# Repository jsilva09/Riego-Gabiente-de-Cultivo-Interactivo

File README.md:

# Riego-Gabiente-de-Cultivo-Interactivo

## Integrantes

- James Mauricio Daza Obando
- Julián Andrés Silva Cuadros
- Ivan Leonardo Tamayo Pérez

## Introducción

El grupo de riego es el encargado de suministrar agua a la planta según sus requerimientos específicos, así como también se encarga de proporcionar los nutrientes básicos necesarios para el correcto desarrollo y crecimiento de la misma.

Se llevará a cabo el método de fertirriego, el cual consiste en suministrar los fertilizantes requeridos por la planta en conjunto con el agua de riego [1]. Este método presenta varias ventajas, entre las cuales se encuentran [2]:

- Se aprovecha un 90% - 95% del agua.
- El agua no se extiende más allá de los límites, como con el uso de aspersores.
- Es más fácil adaptar el sistema a las dimensiones del gabinete propuesto.
- Reduce las enfermedades del follaje y de los frutos al no mojar la planta.
- La aplicación conjunta de los nutrientes con el agua de riego disminuye las pérdidas por lixiviación, incrementa la disponibilidad de los nutrientes y economiza la mano de obra requerida para la aplicación de los fertilizantes.

De manera general, la planta necesita 3 nutrientes esenciales: Nitrógeno, Fósforo y Potasio. Las cantidades y proporciones se ilustran de mejor manera a continuación [3]:

## Toda la información del proyecto realizado se encuentra en la sección [Wiki](https://github.com/jsilva09/Riego-Gabiente-de-Cultivo-Interactivo/wiki).

## Referencias

[1]    Servicio de Información Agroalimentaria y Pesquera, “El fertirriego”, Gobierno de México, 2016. Disponible en: [https://www.gob.mx/siap/articulos/el-fertirriego](https://www.gob.mx/siap/articulos/el-fertirriego)

[2]	Anónimo, “Manual Técnico Buenas Prácticas Agrícolas –Bpa– en La Producción De Tomate Bajo Condiciones Protegidas”, sF. Disponible en: [https://www.fao.org/3/a1374s/a1374s02.pdf](https://www.fao.org/3/a1374s/a1374s02.pdf)

[3]    Alicia, “Nutrientes para las plantas de cannabis: guía para principiantes”, Grow With Jane, 2021. Disponible: [https://growithjane.com/es/nutrientes-cannabis-plantas/](https://growithjane.com/es/nutrientes-cannabis-plantas/)

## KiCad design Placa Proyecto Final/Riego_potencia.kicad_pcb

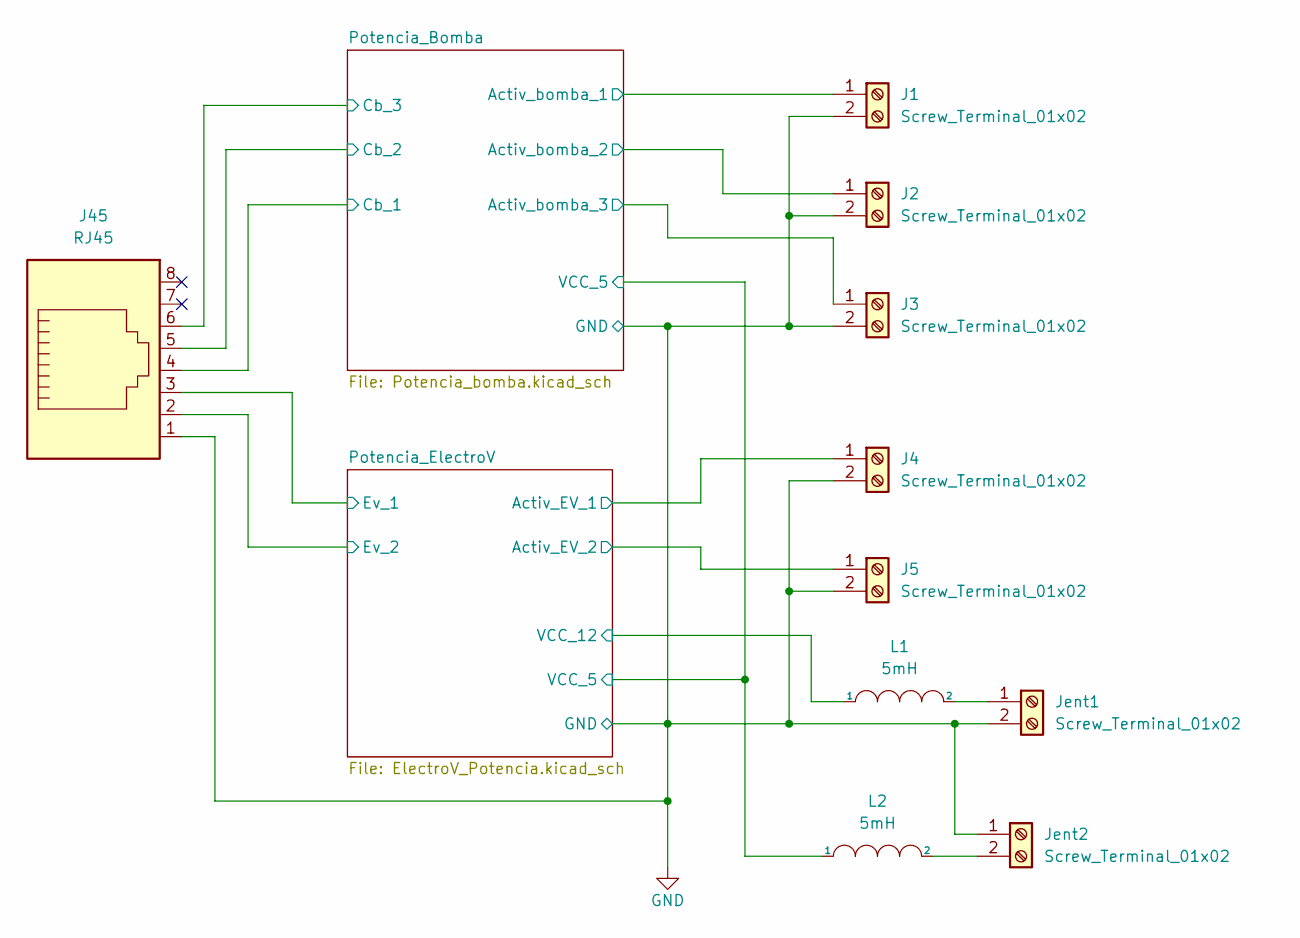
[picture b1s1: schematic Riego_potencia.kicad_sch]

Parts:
J1, J2, J3, J4, J5: Screw_Terminal_01x02; TerminalBlock_Phoenix_MKDS-1,5-2_1x02_P5.00mm_Horizontal
J45: RJ45; RJ45_Amphenol_54602-x08_Horizontal
Jent1, Jent2: Screw_Terminal_01x02; TerminalBlock_Phoenix_MKDS-1,5-2_1x02_P5.00mm_Horizontal
L1, L2: 5mH; L_6.3x6.3_H3

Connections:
/Potencia_Bomba/Activ_bomba_1: J1.1; also elsewhere on the board
/Potencia_Bomba/Activ_bomba_2: J2.1; also elsewhere on the board
/Potencia_Bomba/Activ_bomba_3: J3.1; also elsewhere on the board
/Potencia_Bomba/Cb_1: J45.4; also elsewhere on the board
/Potencia_Bomba/Cb_2: J45.5; also elsewhere on the board
/Potencia_Bomba/Cb_3: J45.6; also elsewhere on the board
/Potencia_Bomba/VCC_5: L2.1; also elsewhere on the board
/Potencia_ElectroV/Activ_EV_1: J4.1; also elsewhere on the board
/Potencia_ElectroV/Activ_EV_2: J5.1; also elsewhere on the board
/Potencia_ElectroV/Ev_1: J45.3; also elsewhere on the board
/Potencia_ElectroV/Ev_2: J45.2; also elsewhere on the board
/Potencia_ElectroV/VCC_12: L1.1; also elsewhere on the board
unnamed: Jent2.2, L2.2

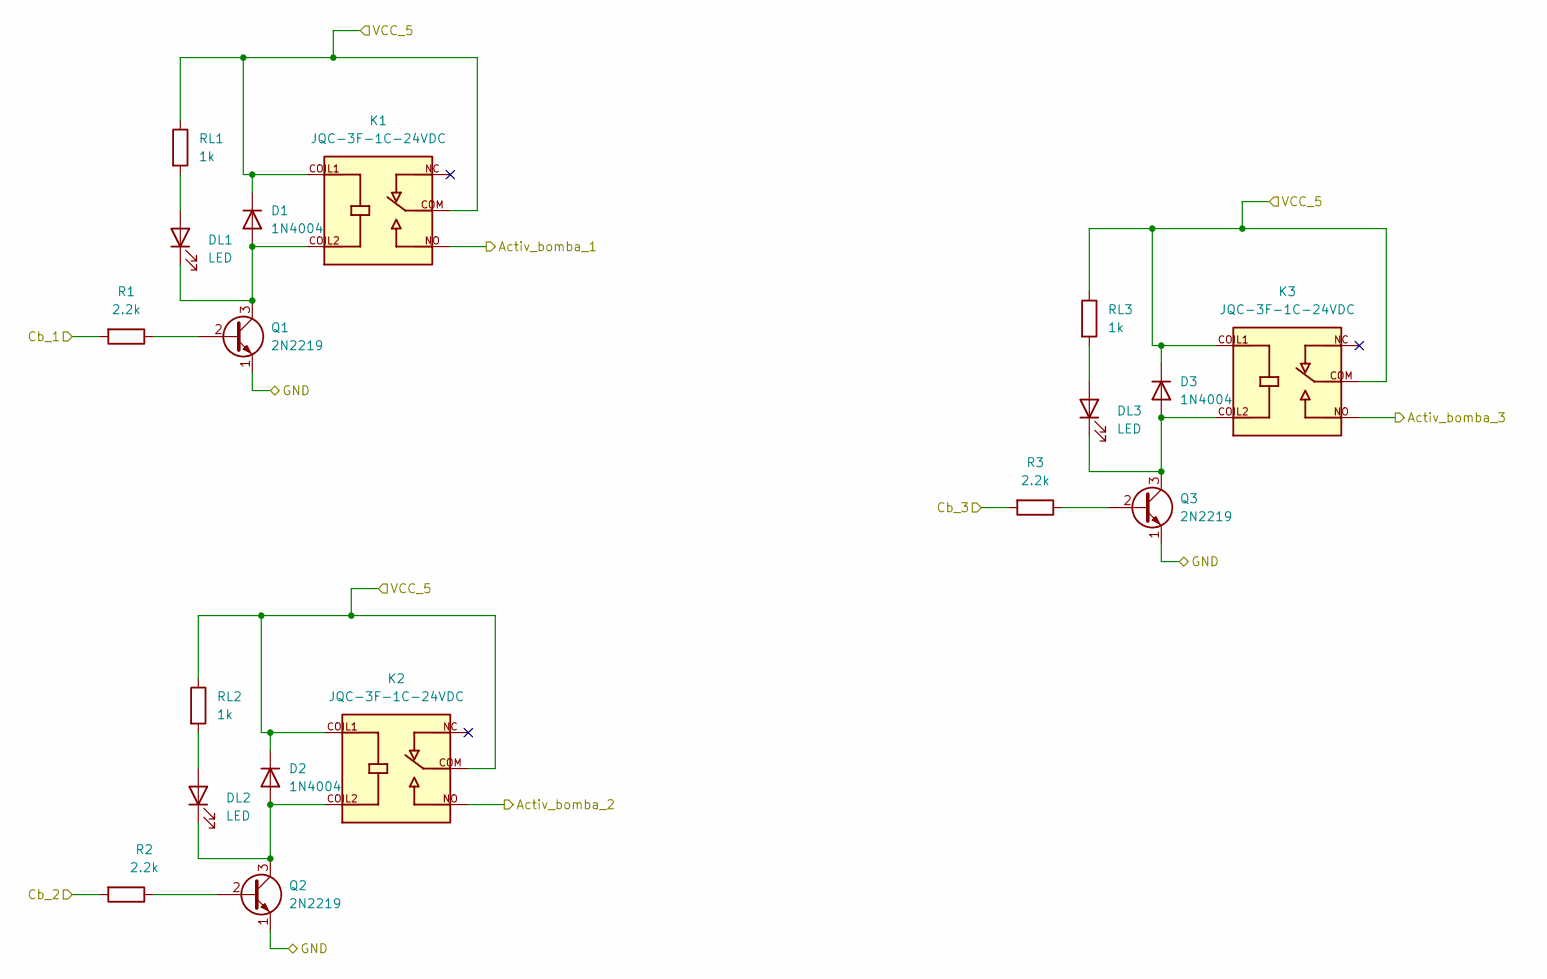
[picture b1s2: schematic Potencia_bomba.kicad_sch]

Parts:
D1, D2, D3: 1N4004; D_2512_6332Metric_Pad1.52x3.35mm_HandSolder
DL1, DL2, DL3: LED; LED_0603_1608Metric_Pad1.05x0.95mm_HandSolder
K1, K2, K3: JQC-3F-1C-24VDC; RELAY_JQC-3F-1C-24VDC; PARTREV N/A
Q1, Q2, Q3: 2N2219; SOT-23
R1, R2, R3: 2.2k; R_0805_2012Metric_Pad1.20x1.40mm_HandSolder
RL1, RL2, RL3: 1k; R_0805_2012Metric_Pad1.20x1.40mm_HandSolder

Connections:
/Potencia_Bomba/Activ_bomba_1: K1.NO; also elsewhere on the board
/Potencia_Bomba/Activ_bomba_2: K2.NO; also elsewhere on the board
/Potencia_Bomba/Activ_bomba_3: K3.NO; also elsewhere on the board
/Potencia_Bomba/Cb_1: R1.2; also elsewhere on the board
/Potencia_Bomba/Cb_2: R2.2; also elsewhere on the board
/Potencia_Bomba/Cb_3: R3.2; also elsewhere on the board
/Potencia_Bomba/VCC_5: D1.1 (K), D2.1 (K), D3.1 (K), K1.COIL1, K1.COM, K2.COIL1, K2.COM, K3.COIL1, K3.COM, RL1.1, RL2.1, RL3.1; also elsewhere on the board
unnamed: D1.2 (A), DL1.1 (K), K1.COIL2, Q1.3 (C)
unnamed: D2.2 (A), DL2.1 (K), K2.COIL2, Q2.3 (C)
unnamed: D3.2 (A), DL3.1 (K), K3.COIL2, Q3.3 (C)
unnamed: DL1.2 (A), RL1.2
unnamed: DL2.2 (A), RL2.2
unnamed: DL3.2 (A), RL3.2
unnamed: Q1.2 (B), R1.1
unnamed: Q2.2 (B), R2.1
unnamed: Q3.2 (B), R3.1

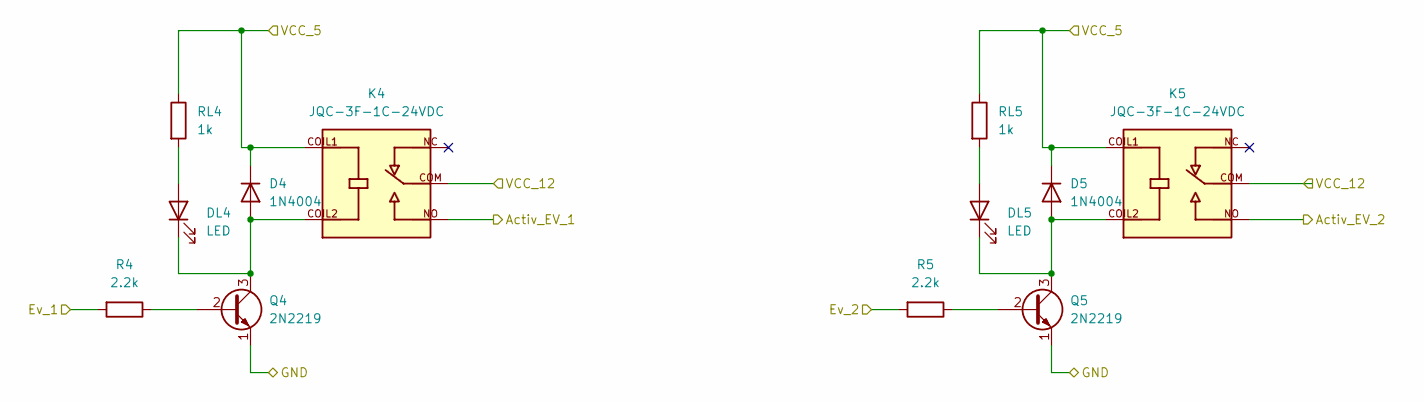
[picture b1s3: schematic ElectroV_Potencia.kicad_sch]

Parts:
D4, D5: 1N4004; D_2512_6332Metric_Pad1.52x3.35mm_HandSolder
DL4, DL5: LED; LED_0603_1608Metric_Pad1.05x0.95mm_HandSolder
K4, K5: JQC-3F-1C-24VDC; RELAY_JQC-3F-1C-24VDC; PARTREV N/A
Q4, Q5: 2N2219; SOT-23
R4, R5: 2.2k; R_0805_2012Metric_Pad1.20x1.40mm_HandSolder
RL4, RL5: 1k; R_0805_2012Metric_Pad1.20x1.40mm_HandSolder

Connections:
/Potencia_Bomba/VCC_5: D4.1 (K), D5.1 (K), K4.COIL1, K5.COIL1, RL4.1, RL5.1; also elsewhere on the board
/Potencia_ElectroV/Activ_EV_1: K4.NO; also elsewhere on the board
/Potencia_ElectroV/Activ_EV_2: K5.NO; also elsewhere on the board
/Potencia_ElectroV/Ev_1: R4.2; also elsewhere on the board
/Potencia_ElectroV/Ev_2: R5.2; also elsewhere on the board
/Potencia_ElectroV/VCC_12: K4.COM, K5.COM; also elsewhere on the board
unnamed: D4.2 (A), DL4.1 (K), K4.COIL2, Q4.3 (C)
unnamed: D5.2 (A), DL5.1 (K), K5.COIL2, Q5.3 (C)
unnamed: DL4.2 (A), RL4.2
unnamed: DL5.2 (A), RL5.2
unnamed: Q4.2 (B), R4.1
unnamed: Q5.2 (B), R5.1

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
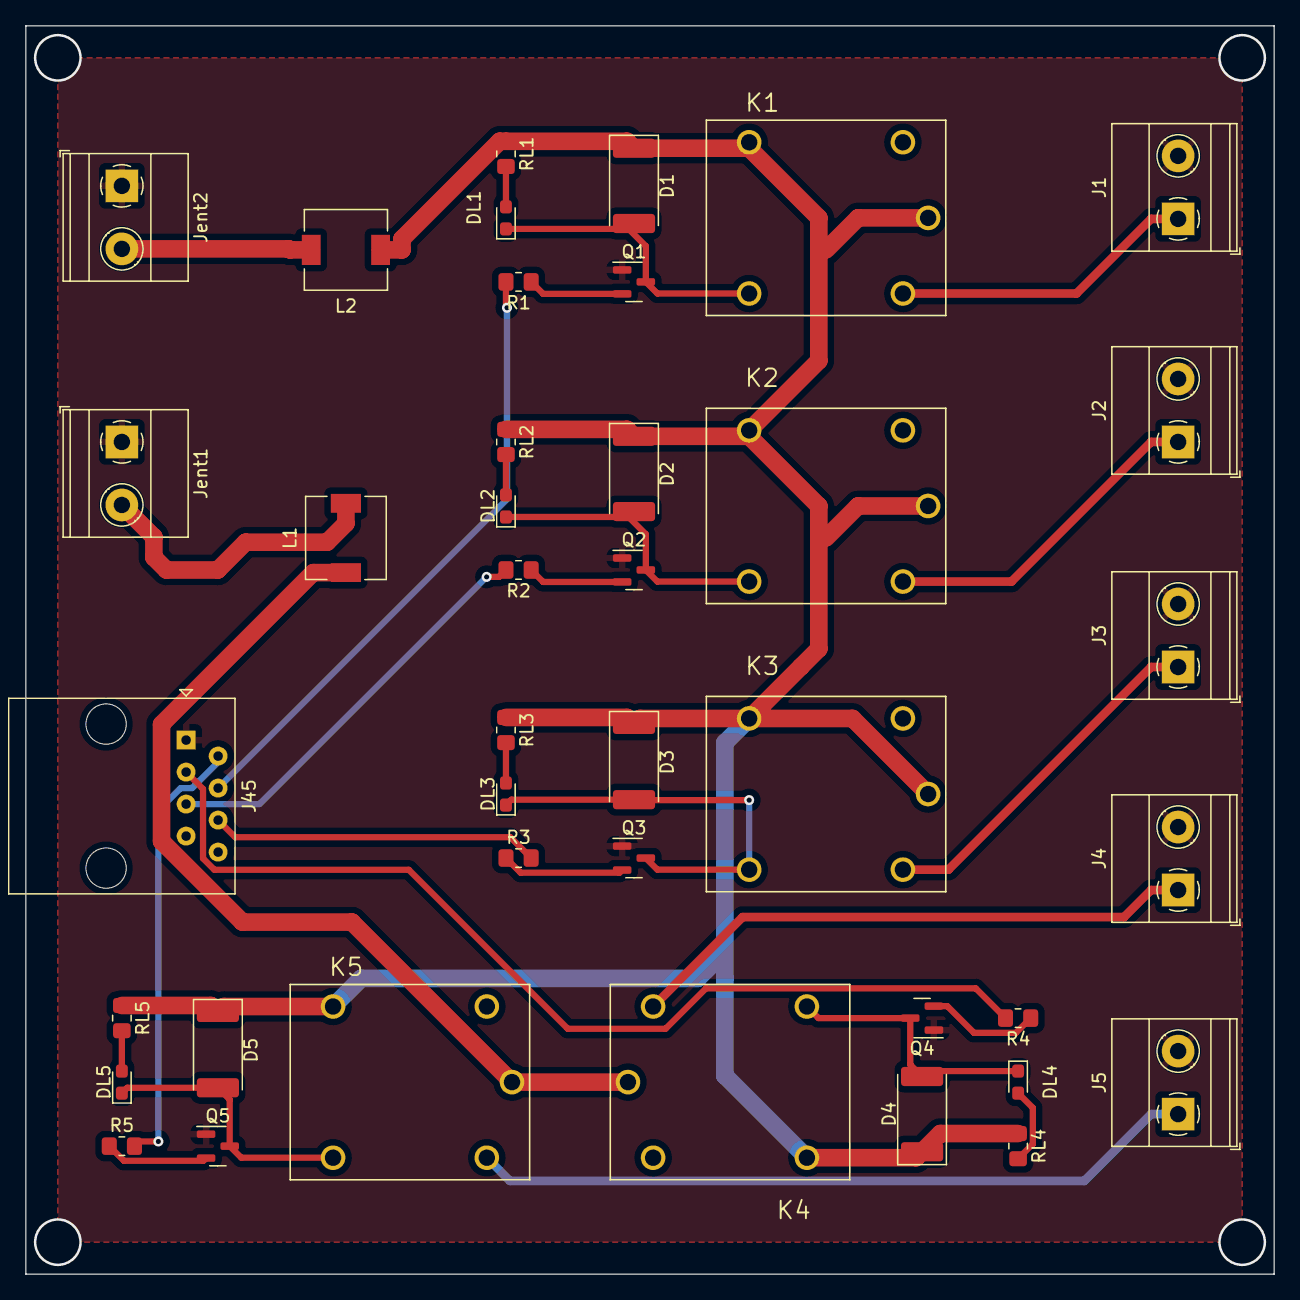
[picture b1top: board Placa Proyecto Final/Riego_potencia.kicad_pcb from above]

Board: 2 copper layers, 99.1 x 99.1 mm, 40 parts (0 on the bottom side), 30 nets.

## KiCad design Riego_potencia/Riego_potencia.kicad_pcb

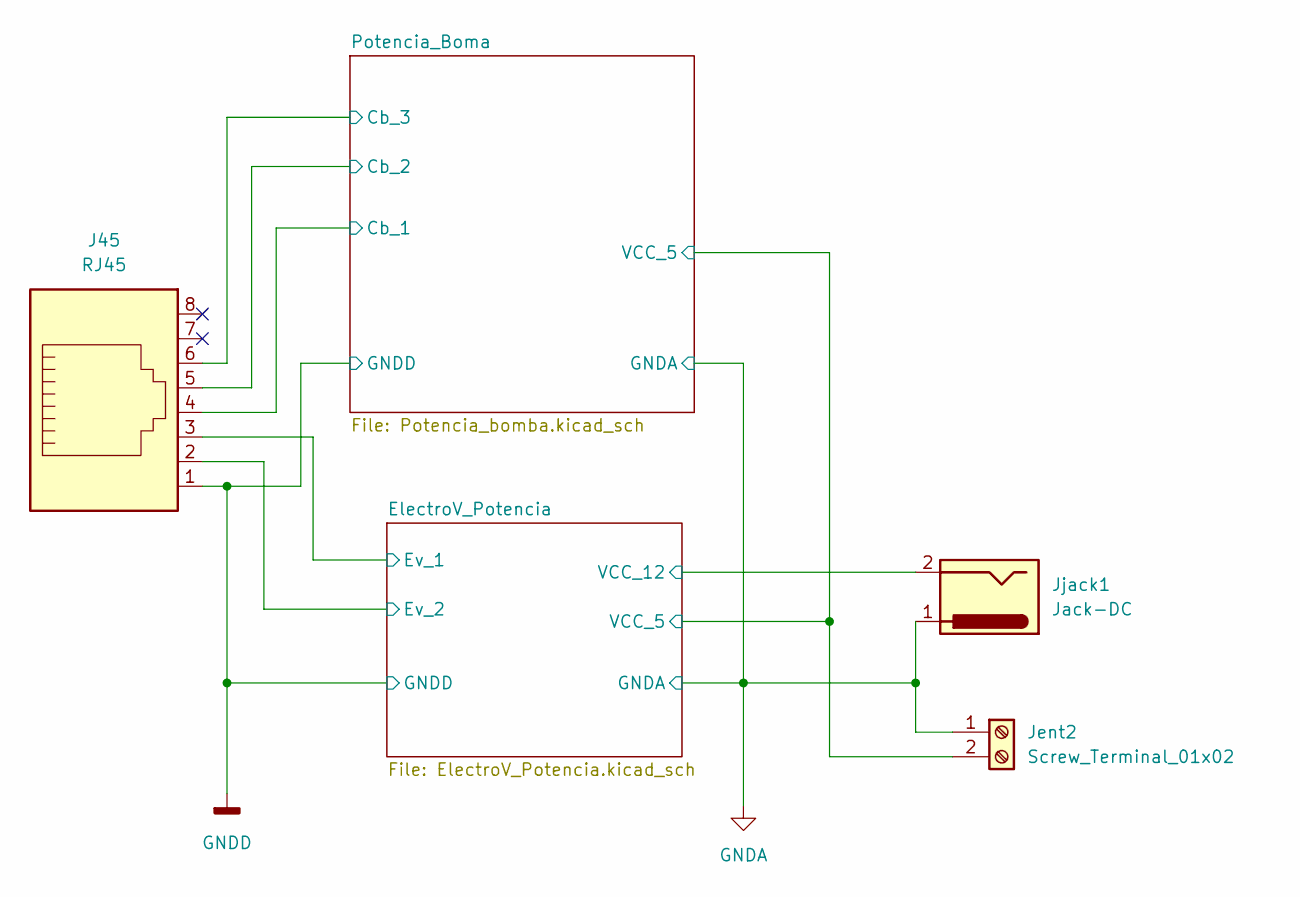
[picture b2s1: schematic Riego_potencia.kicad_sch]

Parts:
J45: RJ45; RJ45_Amphenol_54602-x08_Horizontal
Jent2: Screw_Terminal_01x02; TerminalBlock_Altech_AK300-2_P5.00mm
Jjack1: Jack-DC; BarrelJack_CLIFF_FC681465S_SMT_Horizontal

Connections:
/ElectroV_Potencia/Ev_1: J45.3; also elsewhere on the board
/ElectroV_Potencia/Ev_2: J45.2; also elsewhere on the board
/ElectroV_Potencia/VCC_5: Jent2.2; also elsewhere on the board
/ElectroV_Potencia/VCC_12: Jjack1.2; also elsewhere on the board
/Potencia_Boma/Cb_1: J45.4; also elsewhere on the board
/Potencia_Boma/Cb_2: J45.5; also elsewhere on the board
/Potencia_Boma/Cb_3: J45.6; also elsewhere on the board
GNDD: J45.1, Jent2.1, Jjack1.1; also elsewhere on the board

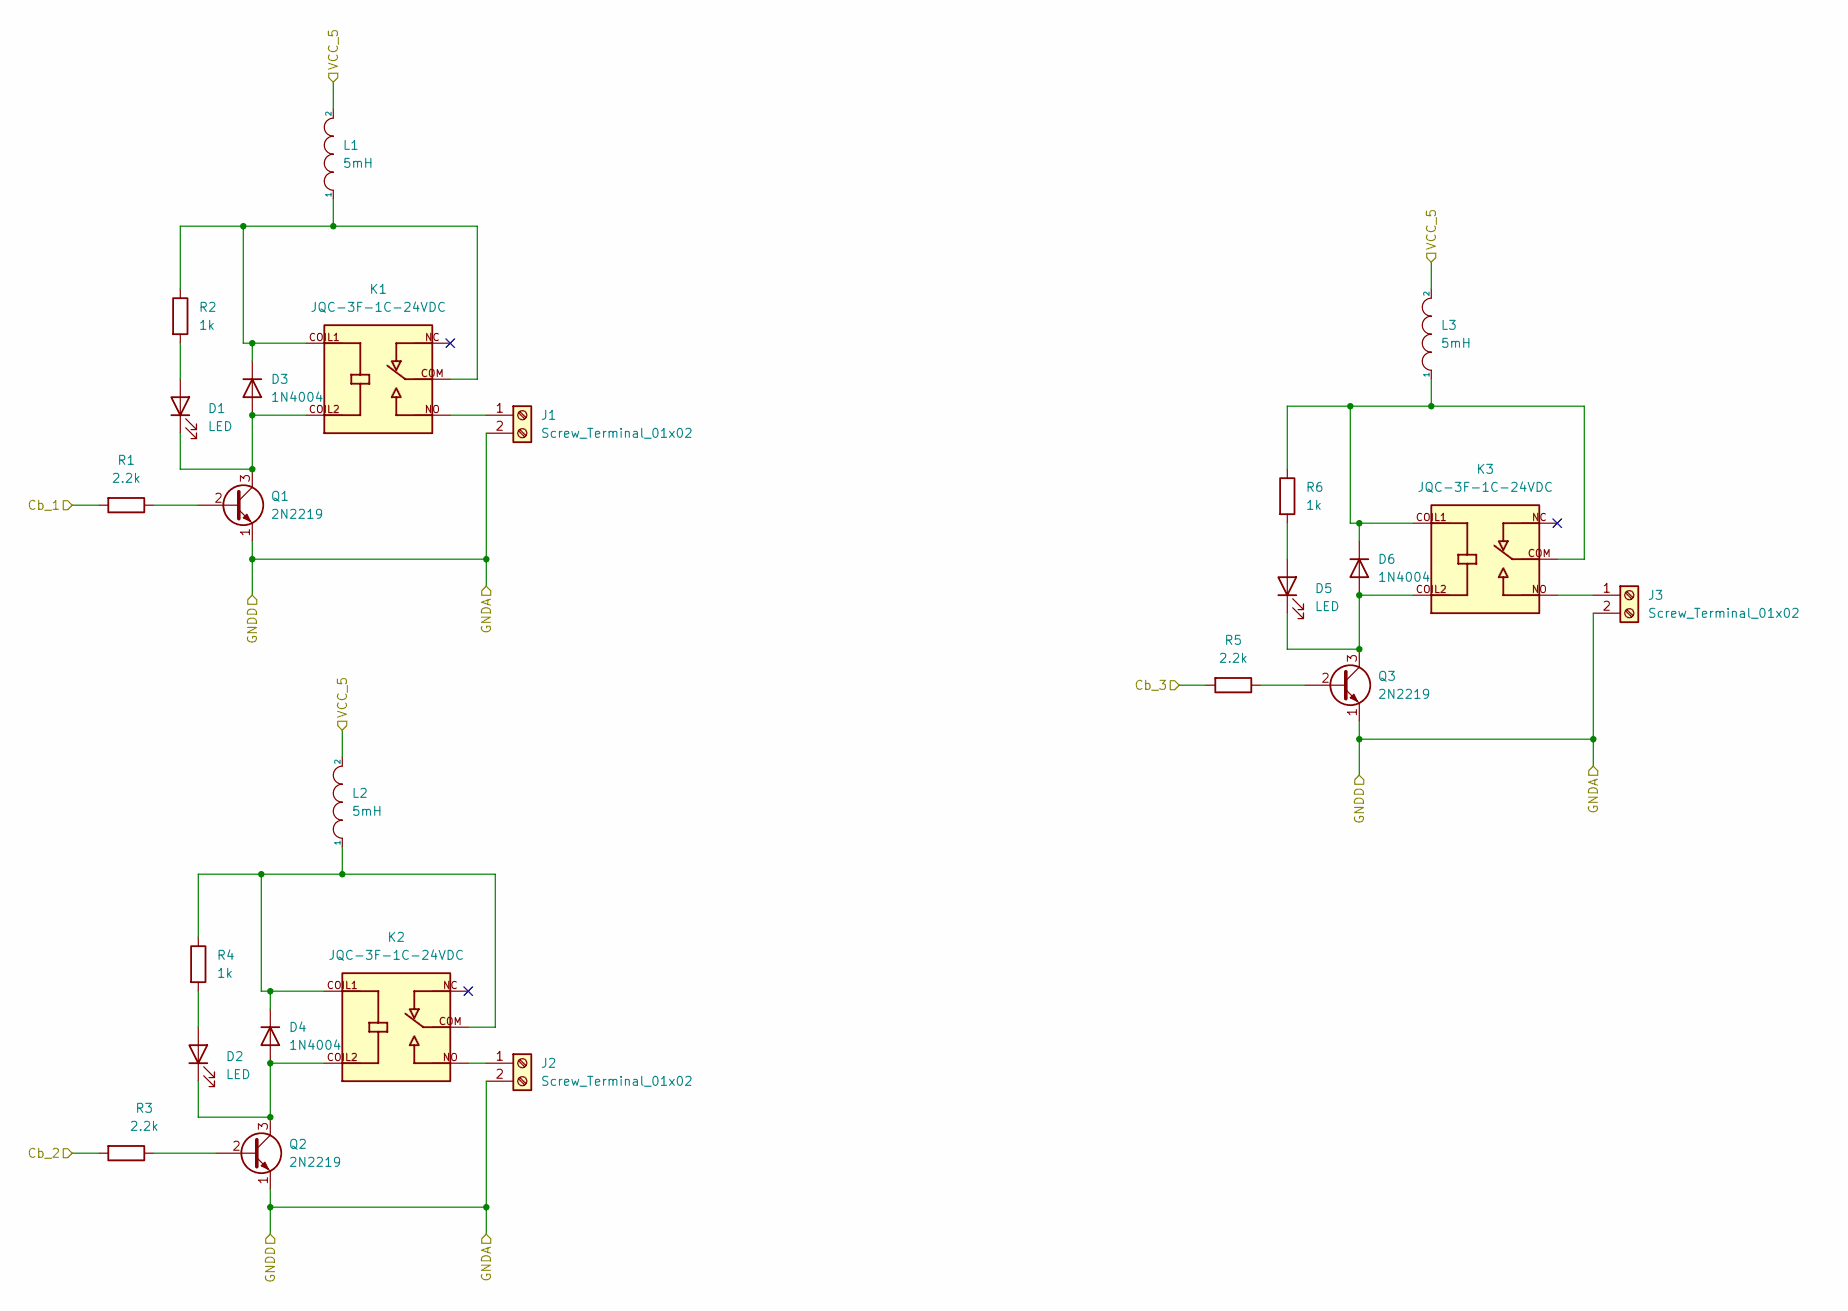
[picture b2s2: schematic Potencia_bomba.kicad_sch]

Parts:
D1, D2, D5: LED; LED_0603_1608Metric_Pad1.05x0.95mm_HandSolder
D3, D4, D6: 1N4004; D_2512_6332Metric_Pad1.52x3.35mm_HandSolder
J1, J2, J3: Screw_Terminal_01x02; TerminalBlock_Altech_AK300-2_P5.00mm
K1, K2, K3: JQC-3F-1C-24VDC; RELAY_JQC-3F-1C-24VDC; PARTREV N/A
L1, L2, L3: 5mH; L_6.3x6.3_H3
Q1, Q2, Q3: 2N2219; SOT-23
R1, R3, R5: 2.2k; R_0805_2012Metric_Pad1.20x1.40mm_HandSolder
R2, R4, R6: 1k; R_0805_2012Metric_Pad1.20x1.40mm_HandSolder

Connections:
/ElectroV_Potencia/VCC_5: L1.2, L2.2, L3.2; also elsewhere on the board
/Potencia_Boma/Cb_1: R1.2; also elsewhere on the board
/Potencia_Boma/Cb_2: R3.2; also elsewhere on the board
/Potencia_Boma/Cb_3: R5.2; also elsewhere on the board
GNDD: J1.2, J2.2, J3.2, Q1.1 (E), Q2.1 (E), Q3.1 (E); also elsewhere on the board
unnamed: D1.1 (K), D3.2 (A), K1.COIL2, Q1.3 (C)
unnamed: D1.2 (A), R2.2
unnamed: D2.1 (K), D4.2 (A), K2.COIL2, Q2.3 (C)
unnamed: D2.2 (A), R4.2
unnamed: D3.1 (K), K1.COIL1, K1.COM, L1.1, R2.1
unnamed: D4.1 (K), K2.COIL1, K2.COM, L2.1, R4.1
unnamed: D5.1 (K), D6.2 (A), K3.COIL2, Q3.3 (C)
unnamed: D5.2 (A), R6.2
unnamed: D6.1 (K), K3.COIL1, K3.COM, L3.1, R6.1
unnamed: J1.1, K1.NO
unnamed: J2.1, K2.NO
unnamed: J3.1, K3.NO
unnamed: Q1.2 (B), R1.1
unnamed: Q2.2 (B), R3.1
unnamed: Q3.2 (B), R5.1

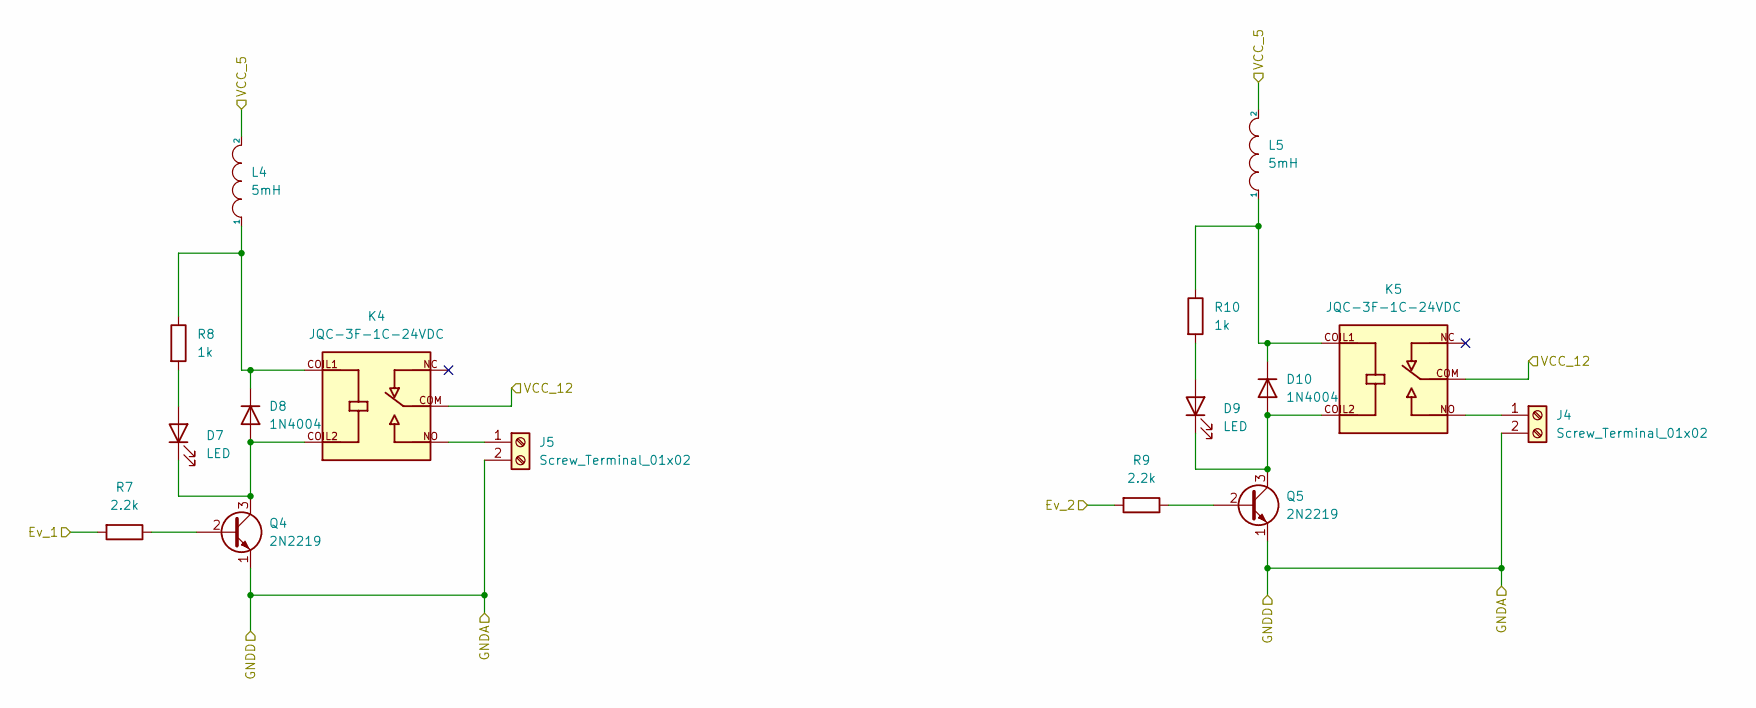
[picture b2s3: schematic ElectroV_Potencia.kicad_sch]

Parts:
D7, D9: LED; LED_0603_1608Metric_Pad1.05x0.95mm_HandSolder
D8, D10: 1N4004; D_2512_6332Metric_Pad1.52x3.35mm_HandSolder
J4, J5: Screw_Terminal_01x02; TerminalBlock_Altech_AK300-2_P5.00mm
K4, K5: JQC-3F-1C-24VDC; RELAY_JQC-3F-1C-24VDC; PARTREV N/A
L4, L5: 5mH; L_6.3x6.3_H3
Q4, Q5: 2N2219; SOT-23
R7, R9: 2.2k; R_0805_2012Metric_Pad1.20x1.40mm_HandSolder
R8, R10: 1k; R_0805_2012Metric_Pad1.20x1.40mm_HandSolder

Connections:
/ElectroV_Potencia/Ev_1: R7.2; also elsewhere on the board
/ElectroV_Potencia/Ev_2: R9.2; also elsewhere on the board
/ElectroV_Potencia/VCC_5: L4.2, L5.2; also elsewhere on the board
/ElectroV_Potencia/VCC_12: K4.COM, K5.COM; also elsewhere on the board
GNDD: J4.2, J5.2, Q4.1 (E), Q5.1 (E); also elsewhere on the board
unnamed: D7.1 (K), D8.2 (A), K4.COIL2, Q4.3 (C)
unnamed: D7.2 (A), R8.2
unnamed: D8.1 (K), K4.COIL1, L4.1, R8.1
unnamed: D9.2 (A), R10.2
unnamed: D10.1 (K), K5.COIL1, L5.1, R10.1
unnamed: D9.1 (K), D10.2 (A), K5.COIL2, Q5.3 (C)
unnamed: J4.1, K5.NO
unnamed: J5.1, K4.NO
unnamed: Q4.2 (B), R7.1
unnamed: Q5.2 (B), R9.1

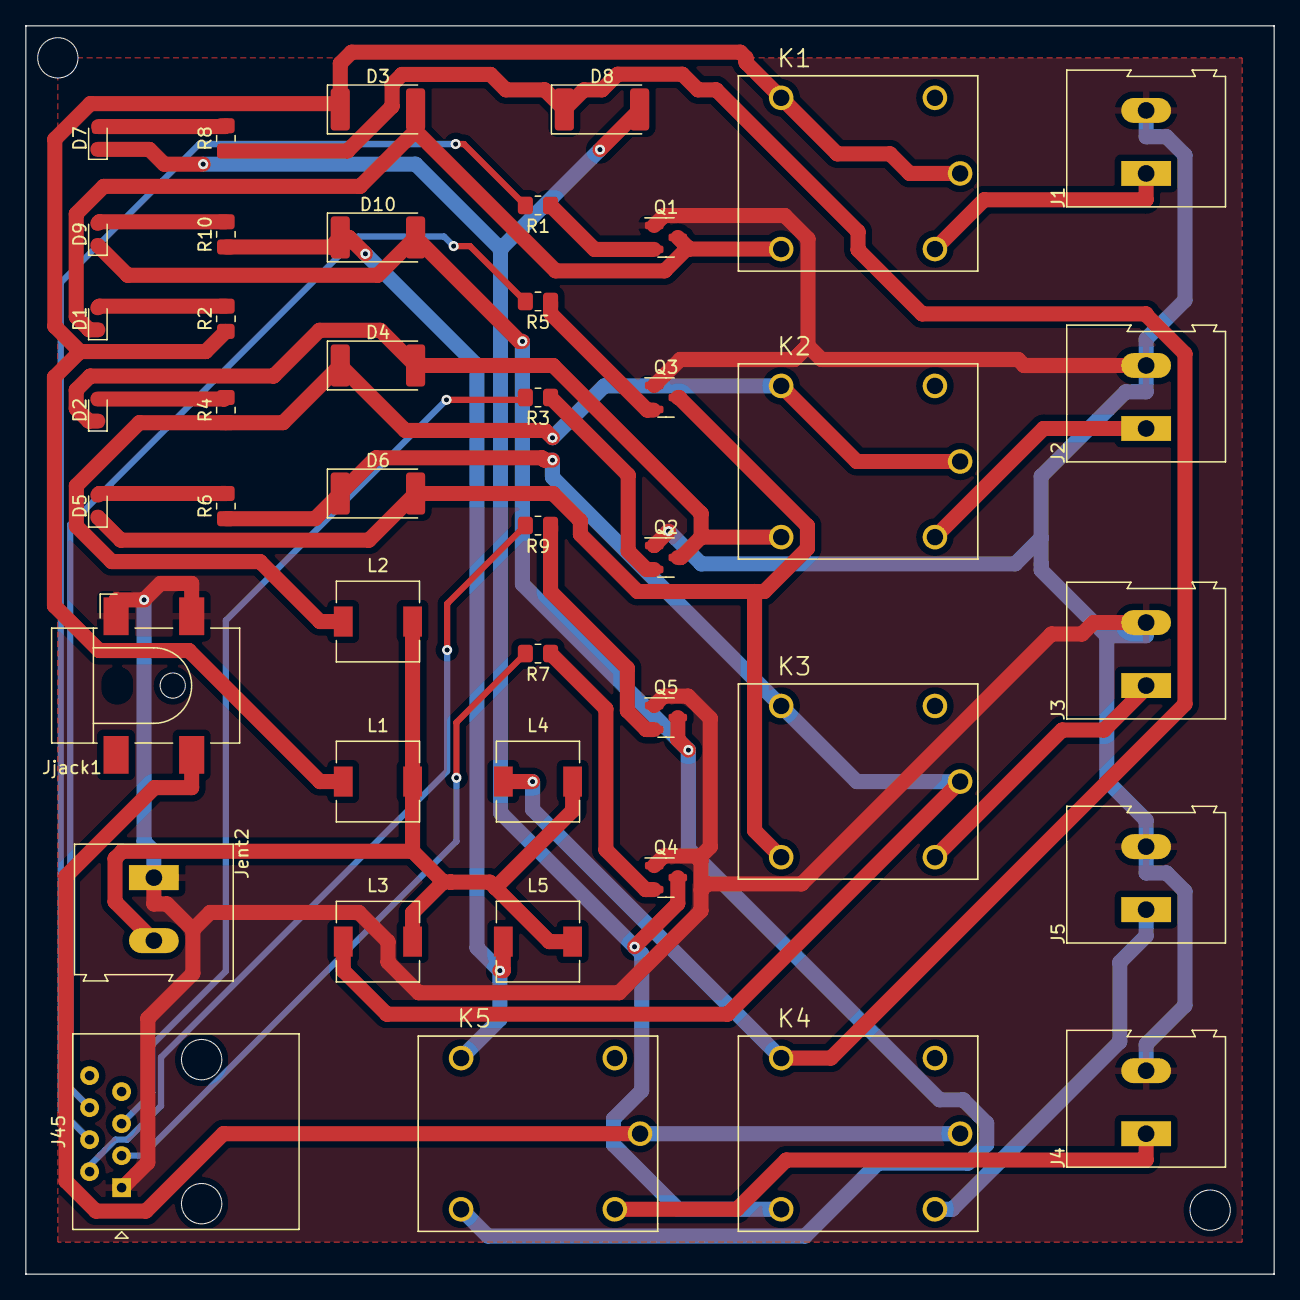
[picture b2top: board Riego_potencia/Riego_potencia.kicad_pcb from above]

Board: 2 copper layers, 99.1 x 99.1 mm, 43 parts (0 on the bottom side), 33 nets.

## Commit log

2022-10-20 Actualizacion
2022-10-22 Create hola
2022-10-22 Nombres
2022-10-25 Nombrar
2022-10-31 Tilde
2022-11-05 Add files via upload
    Imagenes de la carcasa
2022-11-05 Add files via upload
    Gant
2022-11-05 Add files via upload
    Gant_2
2022-11-06 Acualizar
